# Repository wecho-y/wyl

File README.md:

# 我的项目

这是我的 GitHub 项目主页。

## 项目简介

这里介绍我发布的代码、学习资料或毕业设计内容。

## 作者

wyl

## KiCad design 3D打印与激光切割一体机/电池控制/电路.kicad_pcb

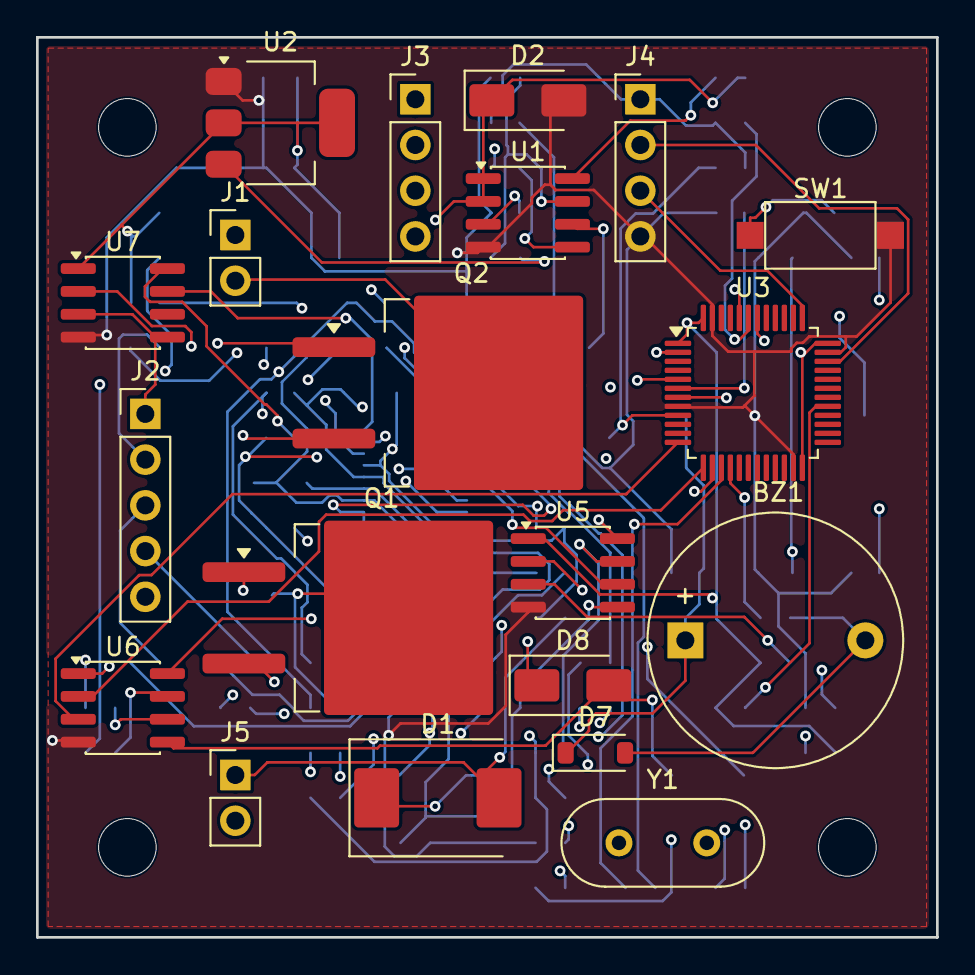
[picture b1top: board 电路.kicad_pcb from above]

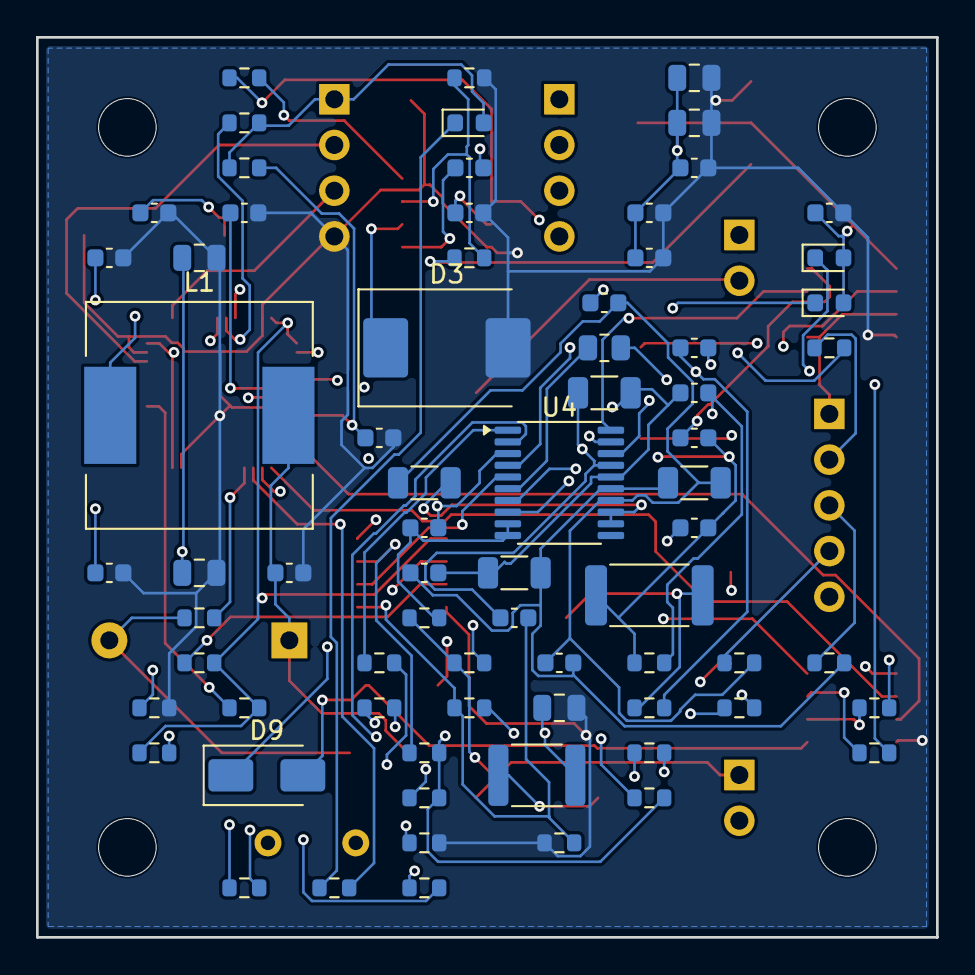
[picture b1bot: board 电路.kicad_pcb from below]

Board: 4 copper layers, 50.0 x 50.0 mm, 96 parts (72 on the bottom side), 62 nets.

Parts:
BZ1: Buzzer_D14mm_H7mm_P10mm
C1, C2, C5, C8, C9, C10, C12, C13, C14, C15, C16, C17, C18, C19, C20, C21, C22, C23, C24, C25, C26: C_0603_1608Metric
C3, C4, C6, C7, C11: C_0805_2012Metric
D1, D3: D_SMC
D2, D8, D9: D_SMA
D4, D5, D6: LED_0603_1608Metric
D7: D_SOD-123
F1: R_1812_4532Metric
FB1: R_0603_1608Metric
H1, H2, H3, H4: MountingHole_3.2mm_M3
J1, J5: PinHeader_1x02_P2.54mm_Vertical
J2: PinHeader_1x05_P2.54mm_Vertical
J3, J4: PinHeader_1x04_P2.54mm_Vertical
L1: L_12x12mm_H8mm
Q1, Q2: TO-263-2
R1, R2, R3, R4, R5, R6, R7, R8, R9, R10, R11, R12, R13, R14, R15, R16, R22, R23, R24, R25, R26, R27, R28, R29, R30, R31, R32, R33, R34, R35, R36: R_0603_1608Metric
R17, R18, R19, R20: R_1206_3216Metric
R21: R_2512_6332Metric
RT1: R_0805_2012Metric
SW1: SW_SPST_CK_RS282G05A3
U1, U5, U6, U7: SOIC-8_3.9x4.9mm_P1.27mm
U2: SOT-223-3_TabPin2
U3: LQFP-48_7x7mm_P0.5mm
U4: TSSOP-20_4.4x6.5mm_P0.65mm
Y1: Crystal_HC49-4H_Vertical

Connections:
ALERT_HV: R32.1, U4.20, U7.7
ALERT_LV: R33.1, U3.29, U7.2
B1: J2.2, R13.1
B2: J2.3, R14.1
B3: J2.4, R15.1
BAT_AFE: C20.1, R11.2, U4.9, U4.10
BOOT0: R6.1, U3.44
BST_N: C2.1, U1.5
BUZZER: R10.2, U3.16
BUZ_N: BZ1.2, D7.2, R10.1
CHG_GATE: R26.1, U4.2
DSG_GATE: R24.1, U4.1
EN_5V: R3.2, R4.1, U1.8
GND: C1.2, C3.2, C4.2, C5.2, C6.2, C7.2, C8.2, C9.2, C10.2, C11.2, C12.2, C13.2, C14.2, C15.2, C16.2, C17.2, D2.2, D3.2, J4.4, R2.2, R4.2, R6.2, R36.1, SW1.2, U1.4, U2.1, U3.8, U3.23, U3.35, U3.47, U5.4, U6.4, U7.4
GND_AFE: C18.2, C19.2, C20.2, C21.2, J2.1, R12.1, R21.1, R23.1, R36.2, RT1.2, U4.3, U5.5, U7.3, U7.5
GND_FC: D8.2, D9.2, J3.2, U6.5
I2C_SCL_HV: R31.1, U4.5, U5.6
I2C_SCL_LV: R29.1, U3.42, U5.3
I2C_SDA_HV: R30.1, U4.4, U5.7
I2C_SDA_LV: R28.1, U3.43, U5.2
ISENSE_HI: Q1.2, R21.2, R22.1
J3_RX: D9.1, J3.4, R35.2
J3_TX: D8.1, J3.3, R34.2
LED_ALARM: R8.2, U3.15
LED_ALARM_K: D5.1, R8.1
LED_HEART: R9.2, U3.2
LED_HEART_K: D6.1, R9.1
LED_RUN: R7.2, U3.14
LED_RUN_K: D4.1, R7.1
MP_VCC: C1.1, U1.3
NRST: C17.1, R5.2, SW1.1, U3.7
OSC_IN: C15.1, U3.5, Y1.1
OSC_OUT: C16.1, U3.6, Y1.2
PACK+: D1.2, J1.1, J2.5, J5.1, R11.1, R16.1
PACK-: J1.2, J5.2, Q2.2
Q1G: Q1.1, R24.2, R25.1
Q2G: Q2.1, R26.2, R27.1
REGOUT: C19.1, U4.8
SRN: C26.2, R23.2, U4.19
SRP: C26.1, R22.2, U4.18
SWCLK: J4.3, U3.37
SWDIO: J4.2, U3.34
SW_MID: Q1.3, Q2.3, R25.2, R27.2
SW_NODE: C2.2, D3.1, L1.1, U1.6
TS1: RT1.1, U4.6
UART_RX_FC: U3.13, U6.2
UART_RX_ISO: R35.1, U6.7
UART_TX_FC: U3.12, U6.3
UART_TX_ISO: R34.1, U6.6
VBAT_D: D1.1, F1.1
VBAT_RAW: C3.1, D2.1, F1.2, R3.1, U1.1, U1.2
VC0: C21.1, C22.2, R12.2, R17.1, U4.17
VC1: C22.1, C23.2, R13.2, R17.2, R18.1, U4.16
VC2: C23.1, C24.2, R14.2, R18.2, R19.1, U4.15
VC3: C24.1, C25.2, R15.2, R19.2, R20.1, U4.14
VC4: C25.1, R16.2, R20.2, U4.12, U4.13
VCAP_2V5: C18.1, R30.2, R31.2, R32.2, U4.7, U5.8, U7.8
VCC3V3: C7.1, C8.1, C11.1, C12.1, C13.1, C14.1, D4.2, D5.2, D6.2, FB1.1, J4.1, R5.1, R28.2, R29.2, R33.2, U2.2, U3.1, U3.24, U3.36, U3.48, U5.1, U6.1, U7.1
VCC5V_FC: J3.1, U6.8
VCC5_INT: BZ1.1, C4.1, C5.1, C6.1, D7.1, L1.2, R1.1, U2.3
VDDA: C9.1, C10.1, FB1.2, U3.9
VFB: R1.2, R2.1, U1.7
